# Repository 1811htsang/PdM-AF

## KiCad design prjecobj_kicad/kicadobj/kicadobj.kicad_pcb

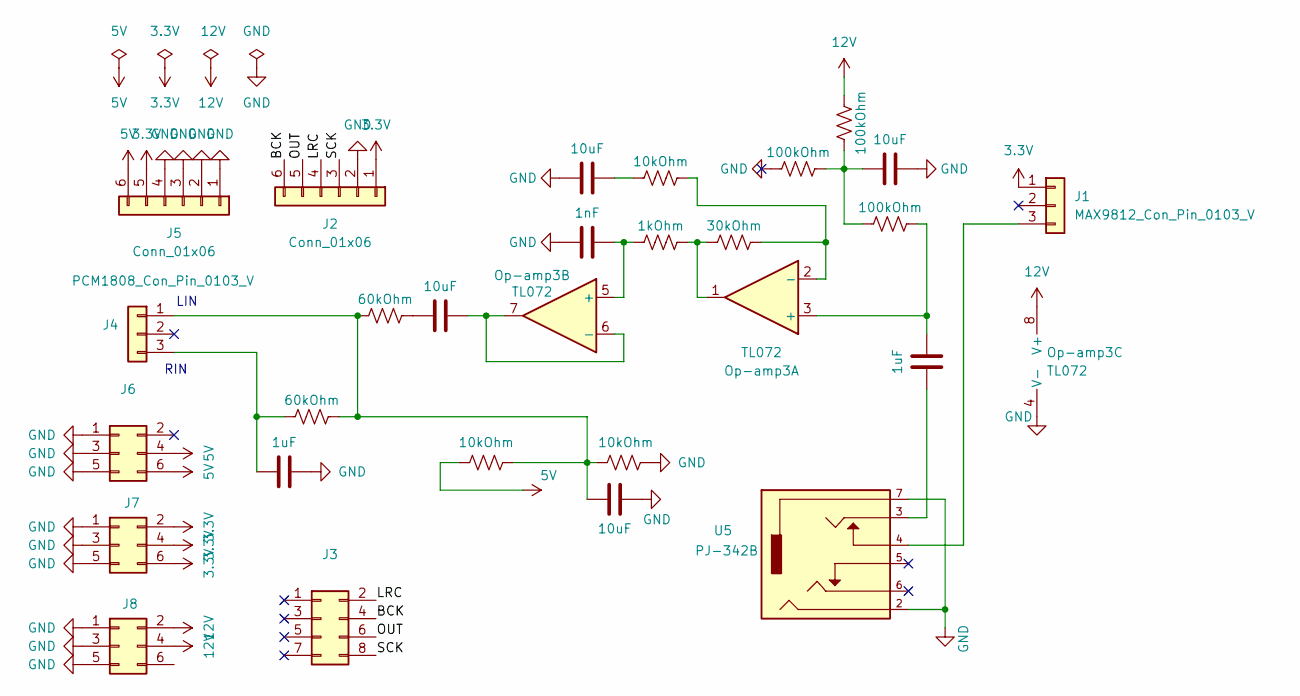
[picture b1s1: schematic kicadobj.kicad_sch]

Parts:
C13, C25, C26, C30: 10uF; C_0805_2012Metric
C23, C31: 1uF; C_0805_2012Metric
C29: 1nF; C_0805_2012Metric
J1: MAX9812_Con_Pin_0103_V; PinHeader_1x03_P2.54mm_Vertical
J2, J5: Conn_01x06; PinHeader_1x06_P2.54mm_Vertical
J3: Conn_02x04_Odd_Even; PinSocket_2x04_P2.54mm_Vertical
J4: PCM1808_Con_Pin_0103_V; PinHeader_1x03_P2.54mm_Vertical
J6, J7, J8: Conn_02x03_Odd_Even; PinSocket_2x03_P2.54mm_Vertical
Op-amp3: TL072; SOIC127P600X175-8N
R2, R3, R32: 10kOhm; R_0805_2012Metric
R26, R27, R29: 100kOhm; R_0805_2012Metric
R30: 30kOhm; R_0805_2012Metric
R31: 1kOhm; R_0805_2012Metric
R33, R34: 60kOhm; R_0805_2012Metric
U5: PJ-342B

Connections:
3.3V: J1.1, J2.1, J5.5, J7.2, J7.4, J7.6
5V: J5.6, J6.4, J6.6, R2.1
12V: J8.2, J8.4, Op-amp3.8 (V+), R27.1
/BCK: J2.6, J3.4
/LRC: J2.4, J3.2
/OUT: J2.5, J3.6
/SCK: J2.3, J3.8
GND: C13.1, C25.2, C29.1, C30.1, C31.2, J2.2, J5.1, J5.2, J5.3, J5.4, J6.1, J6.3, J6.5, J7.1, J7.3, J7.5, J8.1, J8.3, J8.5, Op-amp3.4 (V-), R3.2, R29.1, U5.2, U5.7
unnamed: C23.1, U5.3
unnamed: C25.1, R26.1, R27.2, R29.2
unnamed: C26.1, R33.2
unnamed: C30.2, R32.1
unnamed: J1.3, U5.4
unnamed: C13.2, J4.1, R2.2, R3.1, R33.1, R34.2
unnamed: C31.1, J4.3, R34.1
unnamed: Op-amp3.1, R30.1, R31.2
unnamed: C23.2, Op-amp3.3 (+), R26.2
unnamed: Op-amp3.2 (-), R30.2, R32.2
unnamed: C29.2, Op-amp3.5 (+), R31.1
unnamed: C26.2, Op-amp3.6 (-), Op-amp3.7

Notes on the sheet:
RIN
LIN

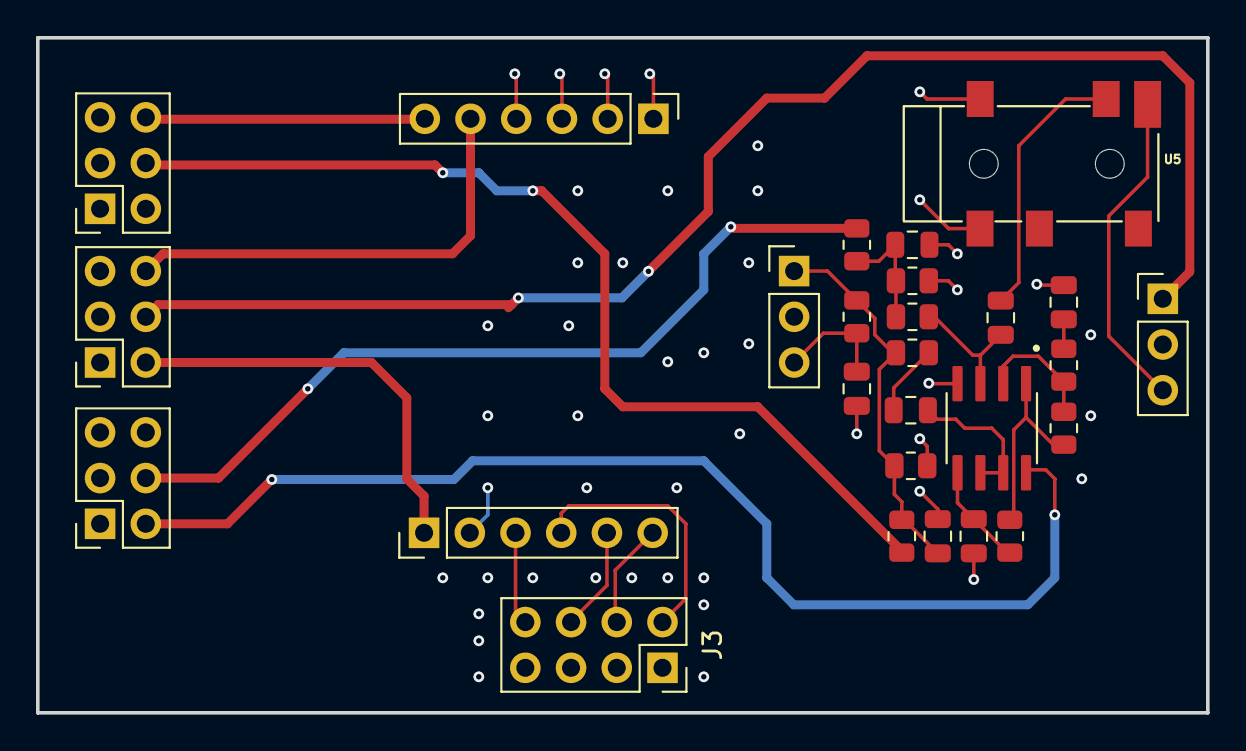
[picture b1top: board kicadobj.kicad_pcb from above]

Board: 2 copper layers, 65.0 x 37.5 mm, 27 parts (0 on the bottom side), 20 nets.
